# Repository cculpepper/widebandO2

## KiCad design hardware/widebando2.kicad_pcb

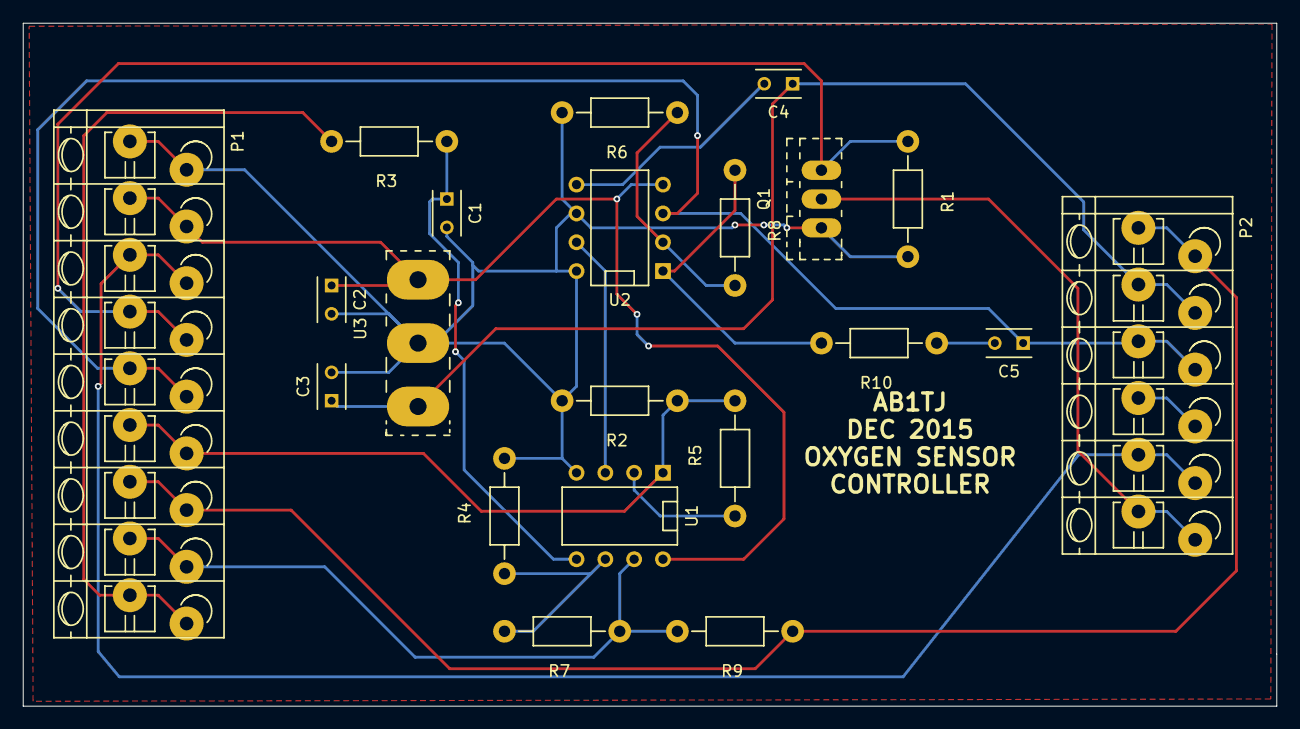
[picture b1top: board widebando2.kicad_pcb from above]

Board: 2 copper layers, 110.5 x 60.2 mm, 21 parts (0 on the bottom side), 19 nets.

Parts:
C1, C2, C3: 1uf; C_Rect_L4_W2.5_P2.5
C4, C5: .5u; C_Rect_L4_W2.5_P2.5
P1: CONN_9; TerminalBlock_WAGO-804_RM5mm_9pol
P2: CONN_6; TerminalBlock_WAGO-804_RM5mm_6pol
Q1: MOSFET_N; TO-220_FET-GDS_Vertical_MountedFromLS_LargePads
R1: 4.7K; Resistor_Horizontal_RM10mm
R2: 1000; Resistor_Horizontal_RM10mm
R3: 15K; Resistor_Horizontal_RM10mm
R4, R6: 10K; Resistor_Horizontal_RM10mm
R5, R7, R8: 20K; Resistor_Horizontal_RM10mm
R9: 1; Resistor_Horizontal_RM10mm
R10: 150; Resistor_Horizontal_RM10mm
U1, U2: TL082; DIP-8__300
U3: 78025; TO-247_Vertical_Neutral123_MountedFromLS_largePads

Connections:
+5V: C2.1, P1.2, U1.8, U2.4, U3.1
+12V: P1.3, P2.5
/HEATERLOW: P2.6, Q1.D
/NernstV: C5.1, P1.5, P2.3, U2.3
/SHUNTHIGH: P1.8, R7.1, R9.2, U1.7
/SHUNTLOW: P1.7, P2.1, R9.1
GND: C1.2, C2.2, C3.2, P1.1, Q1.S, R1.2, R2.2, R4.2, R6.2, U1.4, U2.6, U2.8, U3.2
unnamed: C1.1, R3.1, U1.5
unnamed: C3.1, C4.1, P2.2, U3.3
unnamed: C4.2, U2.5
unnamed: C5.2, R10.1
unnamed: P1.4, Q1.G, R1.1
unnamed: P1.6, R2.1, R5.2, U1.1
unnamed: P1.9, R3.2
unnamed: R4.1, R7.2, U1.6
unnamed: R5.1, U1.2
unnamed: R6.1, R8.2, U2.2
unnamed: R8.1, R10.2, U2.1
unnamed: U1.3, U2.7

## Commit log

2015-11-26 Added a tonne of files from other projects. Almost builds.
2015-11-26 Added a tonne of stuff. Almost builds.
2015-11-26 Fixed a bad thing.
2015-11-30 More generic work. Added an ADC library.
2015-12-03 More work
2015-12-05 Made changes. Should just be tuning.
2015-12-05 Added stuff
2015-12-05 IT WORKS
2015-12-09 Added the PCB
2015-12-09 Added labels
2016-01-27 Using git as a fileserv.r...:X
2016-08-24 Commiting the last of the project
